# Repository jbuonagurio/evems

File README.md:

# Power Quality Analyzer

## Schematic

## Bill of Materials

| Designator                                               | Quantity | Description                                                  | Manufacturer         | Manufacturer Part Number | Digi-Key Part Number        |
| :------------------------------------------------------- | :------: | :----------------------------------------------------------- | :------------------- | :----------------------- | :-------------------------- |
| C1 C2 C4 C5 C6                                           | 5        | Ceramic Capacitor 0.1 μF 25V X7R 0508                        | KYOCERA AVX          | 05083C104KAT2A           | 478-12665-1-ND              |
| C9 C10 C14                                               | 3        | Ceramic Capacitor 1 μF 35V X7R 0805                          | KEMET                | C0805C105K6RACTU         | 399-15007-1-ND              |
| C13 C15 C16                                              | 3        | Ceramic Capacitor 0.1 μF 10V X7R 0603                        | KEMET                | C0603C104K8RACTU         | 399-C0603C104K8RAC7867CT-ND |
| C17 C19 C21 C23                                          | 4        | Ceramic Capacitor 0.1 μF 25V X8R 0603                        | TDK Corporation      | C1608X8R1E104K080AA      | 445-2500-1-ND               |
| C3 C7 C8 C11 C12  C20 C27                                | 7        | Ceramic Capacitor 10 μF 25V X5R 0805                         | KEMET                | C0805C106K3PACTU         | 399-11939-1-ND              |
| C18 C22 C24                                              | 3        | Ceramic Capacitor 4.7 μF 10V X5R 0603                        | KEMET                | C0603C475K8PACTU         | 399-C0603C475K8PAC7411CT-ND |
| C25 C26                                                  | 2        | Ceramic Capacitor 18 pF 50V NP0 0603                         | KEMET                | CBR06C180J5GAC           | 399-CBR06C180J5GACCT-ND     |
| C1A C1B C1C C1N C2A  C2B C2C C2N C3A C3B C3C C4A C4B C4C | 14       | Ceramic Capacitor 0.022 μF 50V C0G 0805                      | TDK Corporation      | C2012C0G1H223J125AA      | 445-7522-1-ND               |
| D1A D1B D1C D1N D2A  D2B D2C D2N                         | 8        | Dual Switching Diode 100V 300mA SOT23                        | Diodes Inc.          | MMBD7000HS-7-F           | MMBD7000HS-7FDICT-ND        |
| J1                                                       | 1        | Header 12 Position 0.100" (2.54mm) RA Through Hole           | Samtec Inc.          | TSW-106-08-L-D-RA        | SAM1041-06-ND               |
| J1A J1B J1C J1N                                          | 4        | 2 Position Terminal Block 0.138" (3.50mm) RA Through Hole    | TE Connectivity      | 284512-2                 | A98396-ND                   |
| J2A J2B J2C                                              | 3        | 2 Position Terminal Block 0.138" (3.50mm) RA Through Hole    | TE Connectivity      | 284391-2                 | A98159-ND                   |
| L1A L1B L1C                                              | 3        | Ferrite Bead 1.5 kΩ @ 100 MHz 0805 250mA 450mΩ               | Murata               | BLM21BD152SN1D           | 490-1048-1-ND               |
| R1                                                       | 1        | Resistor 10 kΩ ±1% 0.1W 0603                                 | Vishay Dale          | CRCW060310K0FKEAC        | 541-5136-1-ND               |
| R1A R1B R1C R1N R2A  R2B R2C R2N R6A R6B R6C R7A R7B R7C | 14       | Resistor 1 kΩ ±0.1% 0.1W 0603 Thin Film                      | YAGEO                | RT0603BRD071KL           | YAG1237CT-ND                |
| R3A R3B R3C R4A R4B  R4C R5A R5B R5C                     | 9        | Resistor 200 kΩ ±0.1% 0.25W 1206 Thin Film                   | Vishay Dale          | TNPV1206200KBEEN         | 541-4632-1-ND               |
| TP1                                                      | 1        | Test Point Miniature                                         | Keystone Electronics | 5015                     | 36-5015CT-ND                |
| U1                                                       | 1        | Digital Isolator 4 Channel 5000VRMS 16SOIC                   | Analog Devices Inc.  | ADUM6404ARIZ             | 505-ADUM6404ARIZ-ND         |
| U2                                                       | 1        | Digital Isolator 4 Channel 3750VRMS 20SSOP                   | Maxim Integrated     | MAX22345SAAP+            | 505-MAX22345SAAP+-ND        |
| U3                                                       | 1        | Linear Voltage Regulator 3.3V 800mA 8-SOIC-EP                | Analog Devices Inc.  | ADM7150ARDZ-3.3          | 505-ADM7150ARDZ-3.3-ND      |
| U4                                                       | 1        | 7 Channel AFE 40-LFCSP-WQ                                    | Analog Devices Inc.  | ADE9000ACPZ              | 505-ADE9000ACPZ-ND          |
| U5                                                       | 1        | Voltage Reference 1.2V ±0.1% 10mA 8-MSOP                     | Analog Devices Inc.  | ADR3512WCRMZ-R7          | ADR3512WCRMZ-R7CT-ND        |
| Y1                                                       | 1        | Crystal 24.576 MHz ±20ppm 12pF 40Ω 4-SMD                     | ECS                  | ECS-245.7-12-33Q-JES-TR  | XC2178CT-ND                 |

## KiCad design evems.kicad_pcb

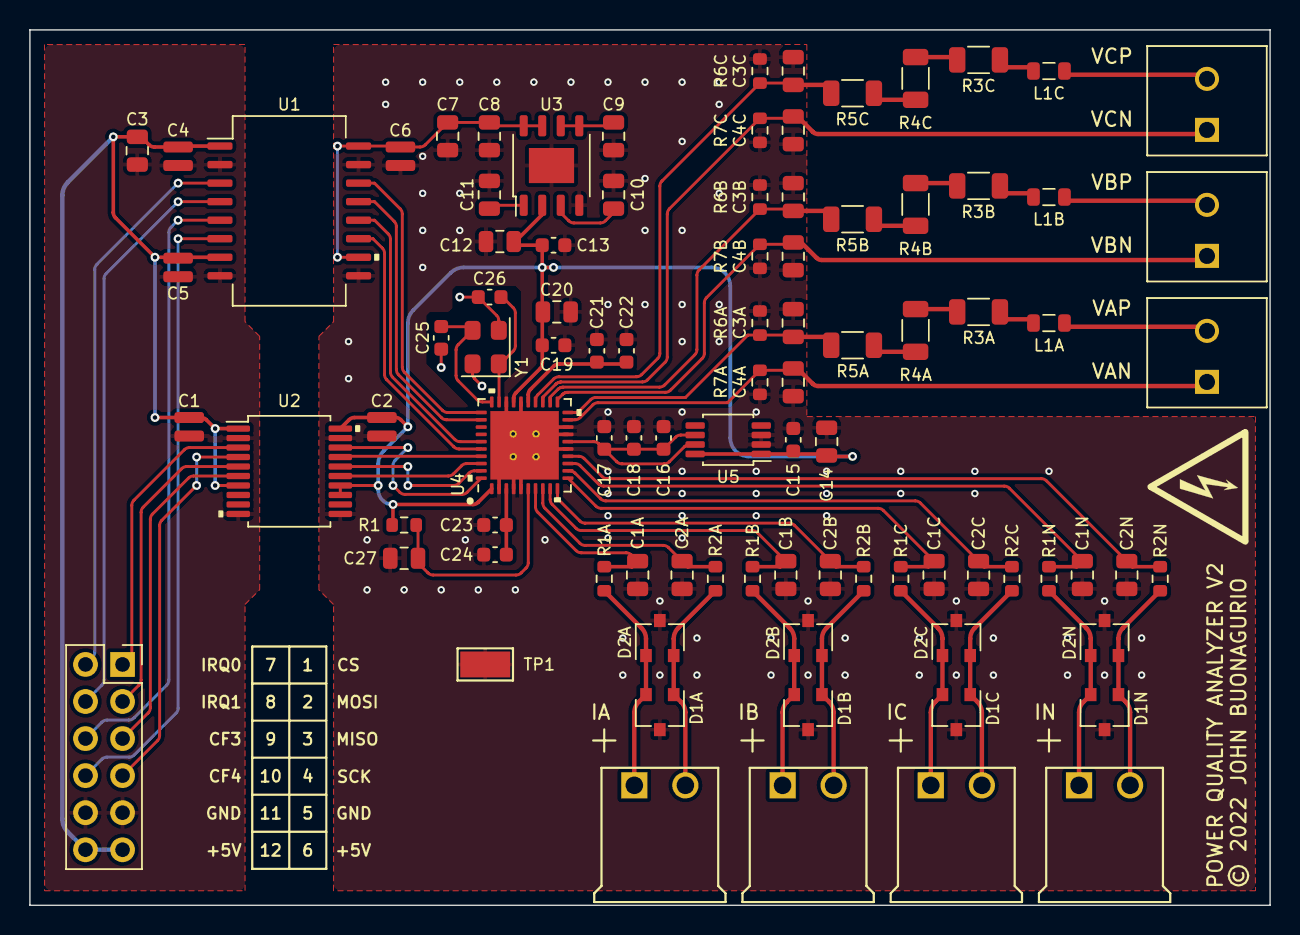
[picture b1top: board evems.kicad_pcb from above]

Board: 2 copper layers, 85.0 x 60.0 mm, 91 parts (0 on the bottom side), 64 nets.

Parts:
C1, C2, C4, C5, C6: 0.1µF; C_0508_1220Metric
C1A1, C1B1, C1C1, C1N1, C2A1, C2B1, C2C1, C2N1, C3A1, C3B1, C3C1, C4A1, C4B1, C4C1: 0.022µF; C_0805_2012Metric
C3, C7, C8, C11, C12, C20, C27: 10µF; C_0805_2012Metric
C9, C10, C14: 1µF; C_0805_2012Metric
C13, C15, C16: 0.1µF; C_0603_1608Metric
C17, C19, C21, C23: 0.1µF 25V; C_0603_1608Metric
C18, C22, C24: 4.7µF; C_0603_1608Metric
C25, C26: 18pF; C_0603_1608Metric
D1A1, D1B1, D1C1, D1N1, D2A1, D2B1, D2C1, D2N1: MMBD4148SE; SC-59
J1: Conn_02x06_Top_Bottom; PinHeader_2x06_Pmod
J1A1, J1B1, J1C1, J1N1: 284512-2; TE_284512-2
J2A1, J2B1, J2C1: 284391-2; TE_284391-2
L1A1, L1B1, L1C1: 1500Ω; L_0805_2012Metric
R1: 10kΩ; R_0603_1608Metric
R1A1, R1B1, R1C1, R1N1, R2A1, R2B1, R2C1, R2N1, R6A1, R6B1, R6C1, R7A1, R7B1, R7C1: 1kΩ; R_0603_1608Metric
R3A1, R3B1, R3C1, R4A1, R4B1, R4C1, R5A1, R5B1, R5C1: 200kΩ; R_1206_3216Metric
TP1: Keystone_5015
U1: ADuM6404ARIZ
U2: MAX22345SAAP+
U3: ADM7150ARDZ-3.3
U4: ADE9000ACPZ
U5: ADR3512WCRMZ-R7
Y1: ECS-245.7-12-33Q-JES-TR

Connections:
/AVDDOUT: C21.1, C22.1, U4.25 (AVDDOUT)
/CF3: U1.12 (V_{IC}), U4.35 (CF3/ZX)
/CF3_{MCU}: J1.9, U1.5 (V_{OC})
/CF4: U1.11 (V_{ID}), U4.36 (CF4/~EVENT/DREADY)
/CF4_{MCU}: J1.10, U1.6 (V_{OD})
/CLKIN: C26.1, U4.29 (CLKIN), Y1.1
/CLKOUT: C25.1, U4.30 (CLKOUT), Y1.3
/DVDDOUT: C23.1, C24.1, U4.3 (DVDDOUT)
/IAN: C2A1.2, R2A1.1, U4.8 (IAN)
/IAP: C1A1.1, R1A1.1, U4.7 (IAP)
/IBN: C2B1.2, R2B1.1, U4.10 (IBN)
/IBP: C1B1.1, R1B1.1, U4.9 (IBP)
/ICN: C2C1.2, R2C1.1, U4.12 (ICN)
/ICP: C1C1.1, R1C1.1, U4.11 (ICP)
/INN: C2N1.2, R2N1.1, U4.14 (INN)
/INP: C1N1.1, R1N1.1, U4.13 (INP)
/IRQ0: U1.14 (V_{IA}), U4.31 (~IRQ0)
/IRQ0_{MCU}: J1.7, U1.3 (V_{OA})
/IRQ1: U1.13 (V_{IB}), U4.32 (~IRQ1)
/IRQ1_{MCU}: J1.8, U1.4 (V_{OB})
/MISO: U2.15 (IN4), U4.38 (MISO)
/MISO_{MCU}: J1.3, U2.6 (OUT4)
/MOSI: U2.16 (OUT3), U4.39 (MOSI)
/MOSI_{MCU}: J1.2, U2.5 (IN3)
/REF: C16.1, C17.1, C18.1, U4.16 (REF), U5.6 (VOUT_FORCE), U5.7 (VOUT_SENSE)
/RESET: C27.1, R1.1, U4.6 (~RESET)
/SCLK: U2.17 (OUT2), U4.37 (SCLK)
/SCLK_{MCU}: J1.4, U2.4 (IN2)
/SS: U2.18 (OUT1), U4.40 (~SS)
/SS_{MCU}: J1.1, U2.3 (IN1)
/VAN: C4A1.2, J2A1.1, R7A1.1, U4.19 (VAN)
/VAP: C3A1.1, R5A1.1, R6A1.2, U4.20 (VAP)
/VBN: C4B1.2, J2B1.1, R7B1.1, U4.21 (VBN)
/VBP: C3B1.1, R5B1.1, R6B1.2, U4.22 (VBP)
/VCN: C4C1.2, J2C1.1, R7C1.1, U4.23 (VCN)
/VCP: C3C1.1, R5C1.1, R6C1.2, U4.24 (VCP)
GND: C1.2, C3.2, C4.2, C5.2, J1.5, J1.11, U1.2 (GND_{1}), U1.8 (GND_{1}), U2.2 (GNDA), U2.10 (GNDA)
GNDA: C1A1.2, C1B1.2, C1C1.2, C1N1.2, C2.2, C2A1.1, C2B1.1, C2C1.1, C2N1.1, C3A1.2, C3B1.2, C3C1.2, C4A1.1, C4B1.1, C4C1.1, C6.2, C7.2, C8.2, C9.2, C10.1, C11.1, C12.1, C13.1, C14.2, C15.2, C16.2, C17.2, C18.2, C19.2, C20.2, C21.2, C22.2, C23.2, C24.2, C25.2, C26.2, C27.2, D1A1.3 (common), D1B1.3 (common), D1C1.3 (common), D1N1.3 (common), D2A1.3 (common), D2B1.3 (common), D2C1.3 (common), D2N1.3 (common), R6A1.1, R6B1.1, R6C1.1, R7A1.2, R7B1.2, R7C1.2, TP1.1, U1.9 (GND_{ISO}), U1.15 (GND_{ISO}), U2.11 (GNDB), U2.19 (GNDB), U3.4 (GND), U3.9 (EPAD), U4.2 (DGND), U4.4 (PM0), U4.5 (PM1), U4.15 (REFGND), U4.17 (NC1), U4.18 (NC2), U4.26 (AGND), U4.28 (GND), U4.41 (EPAD), U5.2 (GND_SENSE), U5.3 (GND_FORCE), Y1.2, Y1.4
unnamed: C6.1, C7.1, C8.1, U1.10 (V_{SEL}), U1.16 (V_{ISO}), U3.7 (EN), U3.8 (V_{IN})
unnamed: C9.1, U3.5 (REF_SENSE), U3.6 (REF)
unnamed: C10.2, U3.3 (BYP)
unnamed: C11.2, U3.1 (V_{REG})
unnamed: D1A1.1 (A), D2A1.2 (K), J1A1.2, R2A1.2
unnamed: D1A1.2 (K), D2A1.1 (A), J1A1.1, R1A1.2
unnamed: D1B1.1 (A), D2B1.2 (K), J1B1.2, R2B1.2
unnamed: D1B1.2 (K), D2B1.1 (A), J1B1.1, R1B1.2
unnamed: D1C1.1 (A), D2C1.2 (K), J1C1.2, R2C1.2
unnamed: D1C1.2 (K), D2C1.1 (A), J1C1.1, R1C1.2
unnamed: D1N1.1 (A), D2N1.2 (K), J1N1.2, R2N1.2
unnamed: D1N1.2 (K), D2N1.1 (A), J1N1.1, R1N1.2
unnamed: J2A1.2, L1A1.2
unnamed: J2B1.2, L1B1.2
unnamed: J2C1.2, L1C1.2
unnamed: L1A1.1, R3A1.2
unnamed: L1B1.1, R3B1.2
unnamed: L1C1.1, R3C1.2
unnamed: R3A1.1, R4A1.2
unnamed: R3B1.1, R4B1.2
unnamed: R3C1.1, R4C1.2
unnamed: R4A1.1, R5A1.2
unnamed: R4B1.1, R5B1.2
unnamed: R4C1.1, R5C1.2
VDD: C1.1, C3.1, C4.1, C5.1, J1.6, J1.12, U1.1 (V_{DD1}), U1.7 (V_{DDL}), U2.1 (V_{DDA}), U2.7 (DEFA)
VDDA: C2.1, C12.2, C13.2, C14.1, C15.1, C19.1, C20.1, R1.2, U2.13 (ENB), U2.14 (DEFB), U2.20 (V_{DDB}), U3.2 (V_{OUT}), U4.1 (PULL_HIGH), U4.27 (VDD), U5.1 (ENABLE), U5.8 (VIN)

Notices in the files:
evems.kicad_pcb:
© 2022 JOHN BUONAGURIO
